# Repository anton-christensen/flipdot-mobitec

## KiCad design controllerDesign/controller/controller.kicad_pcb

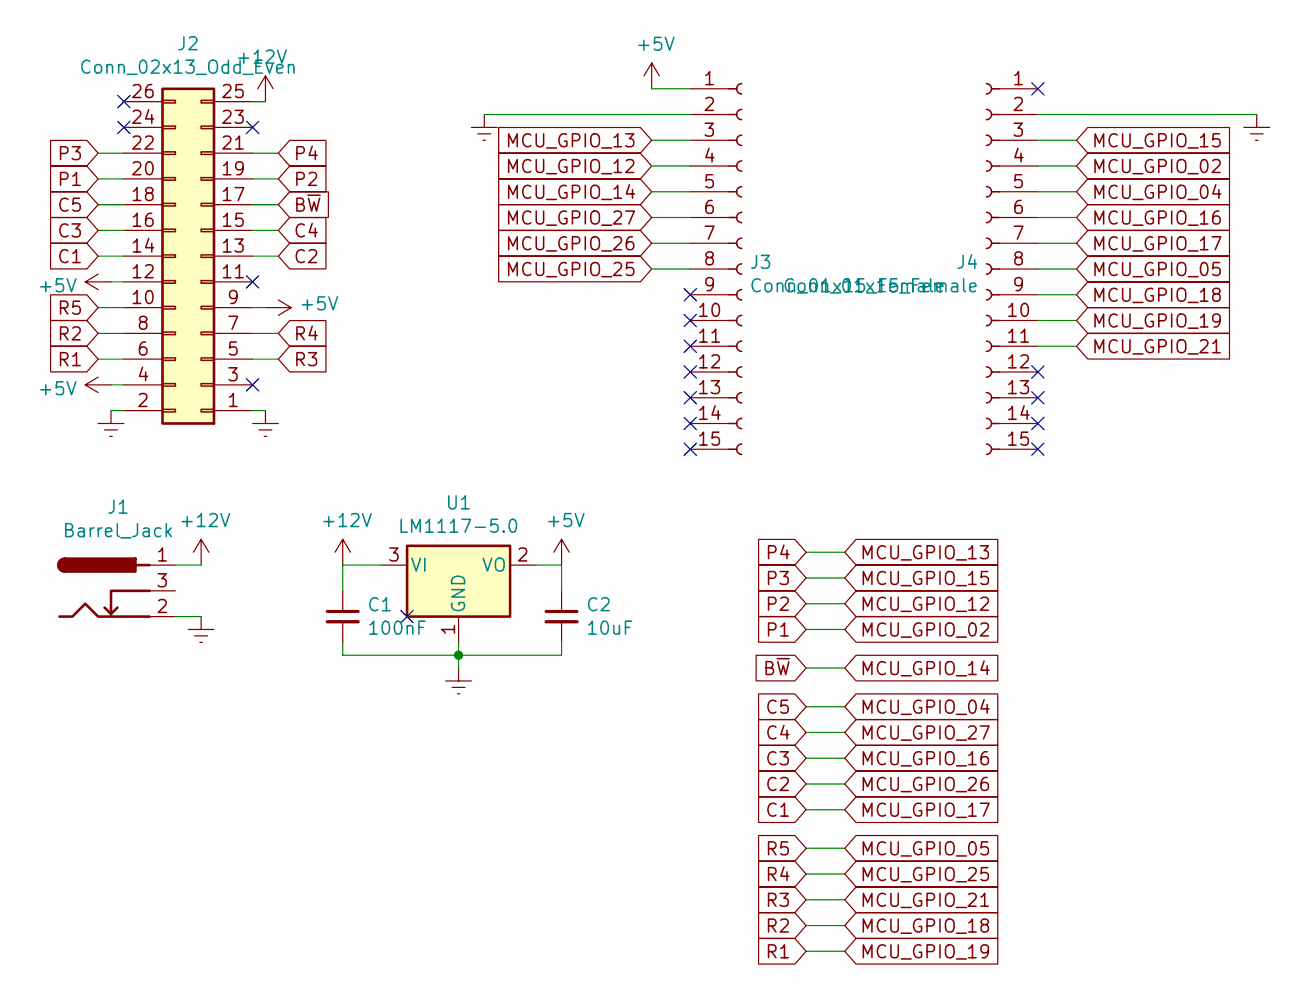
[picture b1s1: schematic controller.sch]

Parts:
C1: 100nF; C_Axial_L12.0mm_D6.5mm_P20.00mm_Horizontal
C2: 10uF; C_Axial_L12.0mm_D6.5mm_P20.00mm_Horizontal
J1: Barrel_Jack; BARREL_JACK
J2: Conn_02x13_Odd_Even; IDC-Header_2x13_Pitch2.54mm_Straight
J3, J4: Conn_01x15_Female; Pin_Header_Straight_1x15_Pitch2.54mm
U1: LM1117-5.0; TO-220-3_Horizontal

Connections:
+5V: C2.1, J2.4, J2.9, J2.12, J3.1, U1.2 (VO)
+12V: C1.1, J1.1, J2.25, U1.3 (VI)
B~W~: J2.17, J3.5
C1: J2.14, J4.7
C2: J2.13, J3.7
C3: J2.16, J4.6
C4: J2.15, J3.6
C5: J2.18, J4.5
Earth: C1.2, C2.2, J1.2, J2.1, J2.2, J3.2, J4.2, U1.1 (GND)
MCU_GPIO_02: J2.20, J4.4
MCU_GPIO_05: J2.10, J4.8
MCU_GPIO_12: J2.19, J3.4
MCU_GPIO_13: J2.21, J3.3
MCU_GPIO_15: J2.22, J4.3
MCU_GPIO_18: J2.8, J4.9
MCU_GPIO_19: J2.6, J4.10
MCU_GPIO_21: J2.5, J4.11
MCU_GPIO_25: J2.7, J3.8

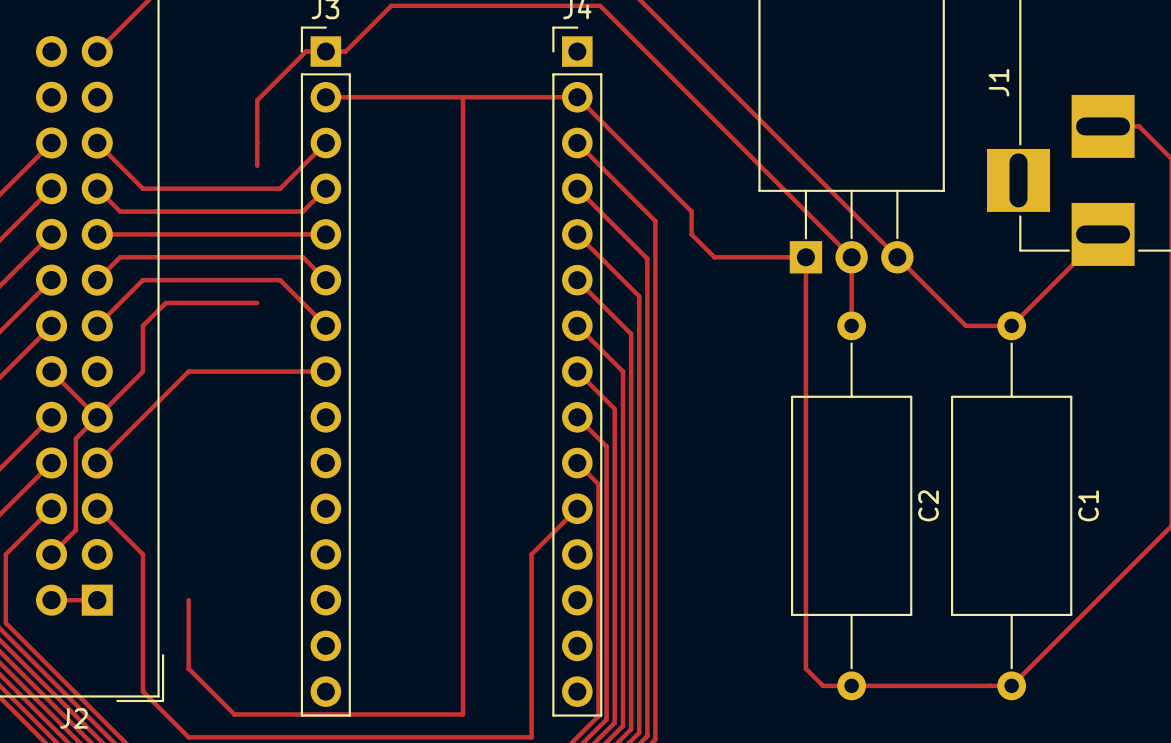
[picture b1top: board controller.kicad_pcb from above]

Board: 2 copper layers, 7 parts (0 on the bottom side), 18 nets.

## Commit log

2018-04-06 Fixes bugs and implements tetris
2018-04-06 reduces flip time
2018-08-14 updates timings
2018-08-19 Adds backlight control
2018-10-13 Moves to i2c gpio expander
2021-01-24 xps backup
